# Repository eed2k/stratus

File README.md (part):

Stratus Weather Server

Version 2.2.1
Developer: Lukas Esterhuizen
Contact: esterhuizen2k@proton.me

Stratus, all software forming part of Stratus, and all associated hardware
designs are the property of METRON (PTY) LTD | Inteltronics. All rights
reserved.

A professional, multi-vendor web application for weather station management, data collection, and real-time monitoring. Stratus connects to Campbell Scientific dataloggers and a range of IoT/cloud weather platforms, then turns raw observations into rich meteorological, agricultural, aviation, fire-risk and wind-energy analytics.

---

Station & Protocol Support

This section is deliberately split into what is running against real hardware
today and what is implemented and mapped but not yet in service here, because the
difference matters when you are choosing how to connect a station.

In production use, exercised against real hardware:

- Campbell Scientific (PakBus) over TCP/IP - native PakBus implementation, including clock sync and scheduled or on-demand collection
  - Supported dataloggers: CR300, CR310, CR350, CR1000, CR1000X, CR1000Xe
- Dropbox sync - watches a folder and ingests a logger export whenever it changes. This is how the cellular sites actually deliver data: the logger writes to Dropbox and Stratus reads it. Read-only; Stratus never writes to your Dropbox
- HTTP POST ingest - the station pushes readings to a per-station endpoint
- Manual file import - TOA5 or CSV upload for bulk history
- RIKA cloud (v2 API) - session login with farm/device discovery, polled every 30 minutes to match the vendor's own update rate

On the RIKA poll specifically: the device endpoint is intermittently slow, and a
half-hourly poll means a single slow response used to cost a full half-hour of
data. Transient faults (timeouts, connection resets, transient DNS, and the busy
gateway statuses 429/502/503/504) are now retried three times with backoff inside
a budget that cannot overlap the next poll. Conditions that would fail identically
on a retry, such as bad credentials, are surfaced immediately instead. A
successful read also clears the last-error line on the settings panel, which
previously persisted through every later healthy poll because it was only ever
cleared when a station reconnected.

Vendor-mapped, implemented but not in production use here:

Each of these has its own response parser and field mapping in
`server/protocols/httpAdapter.ts`, including the unit conversions the vendor's
own units require. They are not bare REST endpoints.

- Arduino IoT Cloud - OAuth2 client-credentials against Thing properties. Properties are matched by name onto temperature, humidity, pressure, wind speed and direction, gust, rainfall, solar radiation, UV, dew point, battery, soil temperature and moisture, PM2.5, PM10 and CO2
- Stratus Logger - Metron's own datalogger board, reporting over LoRa or Sigfox. The LoRa uplink decoder and the generic MQTT/HTTP REST path exist for this board; the hardware design lives in `StratusLoggerV1[metron]/`
- WeatherLink (Davis) - authenticated with an API key and secret, sensor blocks mapped per sensor, with Fahrenheit to Celsius, inches of mercury to hPa and miles per hour to metres per second applied
- CampbellCloud - bearer token, Campbell field names (`AirTemp_C`, `RH`, `BP_mbar`, `WS_ms`, `WD`, `WS_max`, `Rain_mm`, `Solar_Wm2`, `BattV`) mapped to the canonical fields
- ThingSpeak - channel feeds, `field1` through `field8` mapped in the conventional order
- Blynk - token in the query string, virtual pins `V0` through `V5` mapped in order
- OpenWeatherMap - key sent as `appid`, `units=metric` requested when the endpoint does not already specify it, station pressure (`grnd_level`) preferred over the sea-level value, wind direction taken from `wind.deg`, precipitation from the one or three hour rain or snow total, and temperature normalized whether the endpoint returns Celsius, Fahrenheit or Kelvin

One gap, stated plainly rather than implied: bulk station **discovery**
against Campbell Cloud is not implemented. `fetchCampbellStations` raises an
explicit error telling you to use a direct PakBus connection. Collecting data
from a Campbell Cloud endpoint you configure yourself does work, per the mapping
above; it is only the "list every station on the account for me" step that is
absent.

---

Real-Time Monitoring Dashboard

- Live Dashboard - Real-time weather visualization with auto-refresh and data-freshness indicators
- Configurable Layout - Per-user dashboard configuration panel to show/hide and reorder cards
- Auto-Adjusting Sections - Cards and charts hide automatically when their data fields are unavailable
- Current Conditions - All current readings at a glance with last-update time
- Station Map - OpenStreetMap integration showing station location
- Connection Health - Connection status, data freshness, and staleness warnings
- Alarms - Configurable threshold alarms with optional email notifications
- Quick Time Ranges - 1h, 6h, 12h, 24h, 48h, and 7d views
- Interactive Charts - Temperature, humidity, pressure, solar radiation, and rainfall history

Navigation:

The sidebar is text only, with no icons, and every section is permanently
expanded: no disclosure arrows and nothing to collapse. Every destination stays
visible in the same place on every visit, so the menu can be navigated from
memory rather than by opening things to look inside. Indentation carries the
grouping.

Order runs from live monitoring, through what you produce from the data, to
configuration:

1. Active Stations (the landing page, and where every session starts)
2. AS3935 - admin panel, lightning demo, information centre
3. Forecast - overview, dashboard, accuracy
4. Data and Reports - historical export, report generation, report scheduling
5. Settings - station setup, user management, alerts, system settings
6. About Stratus

Chart styling is shared across the estate. The lightning console is Python with
no bundler, but it vendors the same chart library and mirrors the Stratus
conventions (dashed grid at low opacity, no tick marks, no axis lines, matching
stroke weights and the same palette from `shared/chartColors.ts`), so moving
between the two consoles does not feel like moving between two products.

---

Meteorological & Derived Metrics

Stratus computes a large set of derived values from raw observations:

- Dew Point - Magnus formula when not reported by the station
- Sea Level Pressure (QNH) - Hypsometric adjustment from station pressure and altitude (RIKA stations that report SLP directly are handled in reverse)
- Air Density - From temperature, pressure, and humidity
- Density Altitude - With METAR-style flight-category classification
- Reference Evapotranspiration (ETo) - FAO-56 Penman-Monteith
- Water Balance - Rainfall versus ETo
- Heat Index / Wind Chill / Feels-Like - Apparent temperature calculations
- Heat Stress (WBGT) - Wet Bulb Globe Temperature
- Atmospheric Stability - Pasquill-Gifford stability class
- Air Quality Index - AQI from PM2.5 / PM10 (e.g. RIKA particulate sensors)
- Rainfall Intensity & Yearly Totals - With per-station cumulative-counter offset correction
- Weather Trend Analysis - Current values versus historical average

Agriculture:

- Growing Degree Days (GDD) - Accumulated heat units for crop modeling
- Chill Units - Accumulated cold-hours for dormancy/fruiting models

Fire risk:

- Lowveld Fire Danger Index (LFDI) - Official SAWS/Namibia AFIS formula: (BI + WF) x RCF
- Fuel moisture estimation and component fire-danger scoring

---

Nano-Climate Forecast

A separate service at forecast.stratusweather.co.za. Pure-Python FastAPI with
server-rendered SVG, no bundler, capped at 320 MB.

The method is a station's own record CORRECTING a model background, which is why
it is called nano-climate rather than a forecast feed. A mesoscale model knows a
front arrives on Thursday; it does not know this mast sits in a hollow that pools
cold air. The station record is the part that knows.

- Model background - Vaisala Xweather, on by default for a new station with all nine engine variables. Nothing is fetched until a station has coordinates, so an unpositioned station cannot spend the access budget
- Station history - harmonic climatology, damped anomaly persistence and an analog ensemble over a rolling 35-day window. Data older than that does not enter a forecast; the window is deliberate, so a season-old regime cannot dominate the current one
- Learned site correction - `adaptive.py`. A decaying average per station, variable, provider, lead bucket and time-of-day bucket, updated from the station's own verified forecasts
- Verification - MAE, bias, CRPS, rank histograms and reliability diagrams, scored against the station's own observations, with a method-version hash so a change of method is visible rather than averaged into the history

On the learned correction, measured rather than claimed. Across eight months of
Quaggasklip's record, over identical base hours with and without it, at lead
1-24h: solar radiation error fell 17 percent, humidity 2 percent, pressure and
temperature 1 percent each, wind direction unchanged, and wind speed and gust
each rose about 2 percent. It only acts where an offset is a meaningful share of
the error, which is why it declines to touch a variable whose error is mostly
scatter. Rainfall is excluded outright: its error is intermittency, not offset,
and shifting every hour by a learned millimetre invents drizzle on dry days.

Backfilling is how a new station gets a skill history without waiting: forecasts
are re-issued from past base hours using only the data that existed before each
one, so they can be scored immediately. Issued oldest first, which makes a
backfill with the correction enabled a walk-forward test rather than a claim.

---

Wind Analysis & Wind Energy

- Wind Rose Charts - Direction-frequency distribution over 60 min, 24h, 48h periods
- Wind Speed vs Gust (24h) - Fixed 24-hour comparison chart
- Wind Speed Scatter - Polar plot with color-coded speed classes
- Wind Compass - Real-time direction and speed with cardinal labels
- Beaufort Scale - WMO Beaufort classification of current wind
- Crosswind / Headwind - Runway-relative components for aviation
- Turbulence Intensity - From wind-speed standard deviation
- Wind Power Density - Available wind energy (W/m²) using station-specific air density
- Cumulative Wind Energy Potential - Daily kWh/m² with time-interval integration
- Weibull Distribution - Fitted wind-speed distribution
- Annual Energy Production (AEP) - Estimated turbine yield from the Weibull fit

---

Solar & Power Monitoring

- Solar Position Tracking - Sun elevation, azimuth, nautical dawn/dusk
- Solar Radiation - Incoming shortwave with history
- Solar Power Harvest - Estimated harvestable solar energy
- MPPT Charger Monitoring - Solar charge-controller telemetry
- Battery Monitoring - Logger battery voltage with LiFePO4 status and charging detection

---

Lightning Detection System (LDS)

A separate but linked subsystem: an AS3935 lightning sensor on a Raspberry Pi
Zero W reporting into a multi-tenant FastAPI console (Lightning Alert Console
v1.0), deployed alongside Stratus behind the same Traefik proxy.

Detector (Raspberry Pi Zero W + AS3935):

- SPI-attached AS3935 franklin lightning sensor with startup calibration self-check
- Hourly heartbeat plus an immediate ping on every in-range strike, reporting CPU temperature and load
- Low-power configuration: HDMI, Bluetooth and onboard LEDs disabled, CPU governor tuned
- USB gadget ethernet on a fixed address, so a card with no working wifi is still recoverable over the single USB cable
- Provisioned by cloud-init from the SD card boot partition (see `RPiZero SD Card/`)

Admin console:

- Multi-tenant: each client gets its own panel at `/<slug>/`, with a platform-level management console at the root for creating clients and assigning newly-reporting detectors
- Recipients, groups and per-tenant alert configuration with an alert cooldown
- SMS alerts via Clickatell, with a master on/off switch. The gateway is platform infrastructure and is not exposed in client panels
- Monthly PDF reports (WeasyPrint) with vector charts: CPU trend, distance histogram, energy bands, uptime gauge and storm activity
- Event history with per-event delivery detail

Detector provisioning:

A detector files itself under the platform tenant on its first heartbeat and is
invisible to every client panel until an admin assigns it on the platform
console's Detectors page. That is deliberate rather than incidental: an unclaimed
unit has no owning client, so there is no recipient list to consult and no alert
is sent for it. Assigning a unit also re-files its strike history, heartbeat
samples and calibration records, so a client is not handed a live detector whose
past begins on the day of the handover.

Who can see what:

- Stratus Admin may enter any panel. The session is not pinned for them, so their effective tenant follows the URL
- A client login is pinned to its own tenant. A mismatch between the cookie, the user record and the URL is treated as not-signed-in for that panel rather than an error that would confirm the panel exists
- A client admin sees every login in their own panel and may add and remove them
- An operator sees operator and viewer logins only, never administrators, and has no add or remove controls. Knowing which accounts hold admin rights is the useful half of an attack on them
- A viewer sees no login list, matching how the panel already treats a read-only account elsewhere

Creating a login sends nothing. There is no outbound mail path in this console at
all, which a test enforces by asserting no mail library is importable anywhere in
the package: an operator is created with a password the admin chooses and is told
by whatever means the client prefers. Adding an SMS recipient likewise sends no
confirmation message to that number.

POPIA: a recipient's number is masked to its country prefix and last two digits
before it reaches a log, because container logs are rotated to disk, swept into
backups and read by platform staff who have no relationship with the client's
staff. The full number stays in the message log the client is entitled to see on
their own event page, scoped to their tenant.

Storm activity display:

Recorded strikes are grouped into five proximity bands, nearest first, each drawn
as a small cumulonimbus that flashes more often the busier the band. The block
under each cloud gives the strike count with the peak, mean and lowest intensity
recorded in that band.

- Distance bands: `<= 1 km` (overhead), `< 10 km`, `< 20 km`, `< 30 km`, `30-40 km`
- Selectable window from 1 h to 24 h
- Energy bands (Low / Moderate / High / Extreme) are quarters of the sensor's 21-bit full scale

Two measurement caveats are stated on the display itself rather than left to the
reader to discover:

- The AS3935 measures distance but **not bearing**. Nothing in the display is placed in a compass direction, because any angle would be invented. This is why the view is a proximity ordering and not a map.
- Reported "energy" is a relative sensor value for comparing strikes with each other. It is not joules, and it is not calibrated to any physical unit.

Distance is reported in 15 discrete steps at a manufacturer-rated accuracy of
+/- 4 km, so a strike can legitimately land in an adjacent band.

The band aggregation lives in one place, `LDS ADMIN/app/metrics.py::distance_band_summary`.
Both the live dashboard (`/data/strikes`) and the PDF renderer
(`charts.py::storm_bands_svg`) consume it, so the panel and the report cannot
disagree about how many strikes fell in each band.

---

Reports & Data Export

- History & Analysis - View and analyze data across configurable time ranges
- Report Generation - Export to CSV and PDF (server-side PDF with charts, wind roses, summary tables)
- Scheduled Reports - Password-protected /reports portal; daily/weekly/monthly schedules run via node-cron and email PDF reports
- Stratus Digest - Optional scheduled plain-text/HTML digest email (station status, alarms, temperature, rainfall, wind)
- Data Completeness - Coverage metrics highlighting gaps in the record

How a PDF report is laid out:

Page one is ordered so the document identifies itself before it presents any
figures, and so a reader who only wants the numbers never has to page past the
artwork to reach them.

1. Title: `<Station> Weather Data Report | <period>`
2. Site details, one fact per line and no bullets: location, coordinates, elevation in metres AMSL, and the reporting period as absolute dates
3. Two views of the site side by side, each half the text width, both pinned at the station: a close satellite frame for mast surroundings and exposure, and a wider street map for roads and nearby settlements
4. The min / average / maximum / total statistics table

The period appears twice on purpose. The title carries the relative wording
("Last 30 days"), which is what an operator asks for but which stops being true
once the PDF is filed; the details block carries the absolute dates that keep an
archived report self-describing.

The map pin is placed from fractional Web Mercator tile coordinates, so it lands
on the mast rather than at the centre of the fetched tile block. Both frames come
from the same Esri host, which means one egress rule and one tile scheme. Imagery
is never load-bearing: if the tiles cannot be fetched the table simply moves up
the page, because a report missing its site photograph is still a usable report.

There is no heading above the statistics table. It used to repeat the station name
and period already given in the title, and the table's own column headers say what
the columns are. A table continuing onto another page is still marked, so a reader
landing mid-table knows what they are looking at.

Report text is plain regular Arial throughout, in black. No grey, no bold, and no
em or en dashes anywhere in the output.

---

Calibration & Compliance

- Calibration Management - Track calibration records, due dates, and resolution presets (e.g. rainfall tipping-bucket resolution)
- Per-Station Rainfall Offsets - Suppress phantom rain from cumulative counters that pre-date integration
- Compliance Tracking - Data quality flags and certifications
- Audit Logging - Comprehensive logging of security-relevant events

Rainfall interpretation, and why it is configured rather than guessed:

CRBasic programs and cloud vendors record rain in incompatible ways, and the same
number means different things depending on which. A per-interval field holds the
rain for that scan and must be summed. A cumulative counter holds a running depth
and must be differenced. Reading one as the other does not fail loudly; it
silently returns a plausible but wrong total.

So each station carries an explicit `rainfall_type` in `station_calibration`,
maintained from the admin calibration page, and every totalling path reads it:

- `incremental` - sum the values
- `cumulative_yearly` / `cumulative_lifetime` - sum the positive steps, rejecting counter resets and single-sample glitches larger than any real interval of rain
- `tip_count` - multiply raw tips by the station's `tipFactor`

`auto` remains only as a fallback heuristic for a station nobody has configured,
and it is genuinely unreliable on a fast logger: a one-minute per-interval field
that returns to zero between showers looks enough like a counter to be misread.
Measured on Quaggasklip over 30 days, the heuristic reported 14.5 mm where the
configured incremental reading gives 26.3 mm, which is what a direct SQL sum of
the field confirms. Configure the station.

Because that lookup is synchronous against an in-memory snapshot, an empty
snapshot is indistinguishable from "no calibration" at the call site. Report
rendering therefore awaits the snapshot load before totalling anything, so a
report generated moments after a restart cannot quietly take the fallback path.

Field totals are computed server-side with SQL over the full range, never from the
decimated series a chart is drawn from. Decimation drops records, and for an
accumulating quantity a dropped record is dropped rain.

---

Monitoring & Notifications

Email delivery is handled via MailerSend:

- User Invitations - Email invites with secure setup links
- Password Reset - Self-service reset emails (rate limited)
- Alert Notifications - Email alerts when alert thresholds trigger
- Staleness / Downtime Monitor - Optional admin alerts when a station stops sending data
  - Disabled by default (STALENESS_ALERTS_ENABLED=false); enable explicitly per deployment
- Scheduled Reports & Digest - Automated PDF/text emails on a cron schedule
- Professional HTML Templates - Branded, clearly worded messages

---

Shared Dashboards

- Public Sharing - Generate shareable links for stations
- Compact Dashboards - Optional single-screen share links (no scrolling) with primary metric tiles, 1h and 24h wind roses, and live temperature/humidity and battery/solar charts. Ideal for TVs, monitors and laptops
- Password Protection - Optional password for shared dashboards
- Expiration Control - Set expiry dates for shared links
- View-Only Access - Shared viewers cannot edit

---

Security Features

- Rate Limiting - Protection against brute-force login and password-reset attempts
- Secure JWT Tokens - Cryptographically signed tokens with environment-configurable secrets
- Password Hashing - bcrypt with configurable salt rounds
- Input Validation - Zod schema validation on API endpoints
- HTTPS Enforcement - TLS for all traffic
- Session Management - Secure sessions with automatic recovery
- Audit Logging - Security-event logging
- Content Security Policy - The LDS console runs under `script-src 'self'` with no exceptions: chart bundles are vendored rather than pulled from a CDN, and there are no inline scripts
- Secret Scanning - `python deploy/scan_secrets.py` checks every file git could commit (tracked plus non-ignored untracked) for credentials, and exits non-zero on a finding. Run it before pushing
- Not Indexed, Anywhere - every surface refuses search engines on every response type, not only on its HTML. A meta tag reaches a crawler that parses markup; it does nothing for a JSON endpoint, a generated PDF, a chart image or a redirect. So `X-Robots-Tag: noindex, nofollow, noarchive, nosnippet, noimageindex, notranslate` is set by the server on all five surfaces, backed by a meta tag on the pages and a `robots.txt` on every host. Shared dashboard links are covered by the same header

TLS is issued and renewed by Traefik alone, from its own ACME store. Nothing else
on the host may hold a certificate for these names: a second ACME client cannot
succeed, because Traefik owns ports 80 and 443, and every failed validation it
makes counts against Let's Encrypt's per-hostname failure limit for the same
names Traefik has to renew. A leftover certbot installation was doing exactly
that and is now disabled and masked.

Credentials are kept out of the repository by design. Anything holding a real
secret is gitignored and shipped as a `.example` template instead: the detector's
cloud-init files (wifi PSK, user password hash) and every `.env` variant. A
credential committed once stays recoverable from git history even after the file
is deleted, so the safer default is never to commit it.

---

User Management

- Admin and User Roles - Admins have full access; users see only assigned stations
- Station Assignment - Assign specific stations to individual users
- User Invitation System - Invite via email with secure setup links
- Password Reset - Self-service reset via email (rate limited)
- Account Settings - Self-service profile and password management

---

Hosting

Stratus is designed for cloud VPS deployment for 24/7 availability.

- Recommended: Vultr, Hetzner, Linode, DigitalOcean
- 1-2 vCPU, 2-4 GB RAM sufficient
- Docker containerized deployment (Traefik reverse proxy)
- PostgreSQL database (Neon serverless supported; SQLite supported for local development)
- Automatic restart on failure

---

Environment Variables

Key environment variables (see .env.example for the full annotated list):

```
# Database (Required)
DATABASE_URL=postgresql://user:password@host:port/database

# Server
PORT=5000
NODE_ENV=production

# Security (Required in production)
CLIENT_JWT_SECRET=<generate with: openssl rand -hex 32>
APP_BASE_URL=https://yourdomain.com

# Admin Account (Required in production)
STRATUS_ADMIN_EMAIL=admin@example.com
STRATUS_ADMIN_PASSWORD=<strong-password>
STRATUS_ADMIN_NAME=Admin User

# Email (MailerSend - optional)
MAILERSEND_API_KEY=your_api_token
MAILERSEND_FROM_EMAIL=noreply@yourdomain.com
MAILERSEND_FROM_NAME=Stratus Weather
MAILERSEND_ALERTS_EMAIL=alerts@yourdomain.com

# Scheduled Digest (optional, requires MailerSend)
DIGEST_ENABLED=true
DIGEST_RECIPIENT=recipient@yourdomain.com
DIGEST_CRON=0 8 * * 1,5   # Mon/Fri 08:00 (Africa/Johannesburg)

# Staleness / Downtime Monitor (optional, disabled by default)
STALENESS_ALERTS_ENABLED=false
STALENESS_CHECK_INTERVAL=900000   # 15 min
STALENESS_THRESHOLD=7200000       # 2 h
STALENESS_COOLDOWN=21600000       # 6 h

# Dropbox Integration (optional)
DROPBOX_APP_KEY=your_app_key
DROPBOX_APP_SECRET=your_app_secret
DROPBOX_REFRESH_TOKEN=your_refresh_token
DROPBOX_FOLDER_PATH=/CR300/Data
```

---

Project Structure

```
client/             React frontend (Vite + TypeScript + Tailwind)
  src/
    components/     UI components (dashboard cards, charts, station setup, sidebar)
    pages/          Route pages (Dashboard, History, Reports, Alarms, Calibration, Settings, ...)
    hooks/          Custom React hooks (useAuth, useMobile)
    lib/            Utility functions and constants
server/             Express backend (TypeScript)
  campbell/         PakBus protocol and datalogger management
  compliance/       Audit and compliance routes
  parsers/          TOA5/Campbell data parsers
  protocols/        Protocol manager + HTTP/LoRa adapters (Rika, Arduino, Campbell, WeatherLink, ...)
  services/         Dropbox sync, email, staleness monitor, report scheduler, digest, PDF, calibration
  shares/           Shared dashboard routes
  station-setup/    Connection validation, service detection, integration service
shared/             Shared types and utilities
  utils/            Calculation functions (LFDI, solar, ETo, air density, AQI, WBGT, Weibull, AEP, ...)
assets/             Application icons
deploy/             Deployment scripts, Docker config, backups, secret scanner
scripts/            Dropbox auth and documentation generation

forecast/           Nano-climate forecast service (separate deployment)
  app/              FastAPI + Jinja2, server-rendered SVG charts, no bundler
    engine.py       Blending, harmonics and the analog ensemble
    adaptive.py     Learned per-site bias correction (see below)
    plain.py        Plain-language outlook (day cards and sentences)
    providers/      NWP adapters (Xweather only) and the per-variable opt-in
  tests/            pytest suite
  README.md         What it is, which models it uses, how to read it

info-centre/        Static documentation site (nginx)
lightning-demo/     Static lightning demo site (nginx)
Beacon/             Pilot-light/beacon controller for the lightning system
Emulator/           Bench emulator for the AS3935 detector (Arduino + Pi)
BeagleBone/         Kiosk that boots a BBB into a wall dashboard over HDMI

StratusLoggerV1[metron]/  Stratus Logger hardware design (KiCad): the in-house
                          datalogger board, LoRa/Sigfox uplink
AS3935/             Lightning detector (Pi Zero W + AS3935) firmware
AS3935handheld/     Handheld lightning detector hardware design (KiCad)
RPiZero SD Card/    Detector boot partition: service, installer, config.txt with
                    SPI enabled and the low-power options, cloud-init templates
                    as *.example (the real files hold credentials and are
                    gitignored), and FLASH_FROM_SCRATCH.md

LDS ADMIN/          Lightning Alert Console (FastAPI, separate deployment)
  app/
    routes/         Web pages, JSON data endpoints, detector ingest API
    templates/      Jinja2 templates (server-rendered, no SPA)
    static/         style.css, app.js, js/cpu-chart.js, js/storm-view.js
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
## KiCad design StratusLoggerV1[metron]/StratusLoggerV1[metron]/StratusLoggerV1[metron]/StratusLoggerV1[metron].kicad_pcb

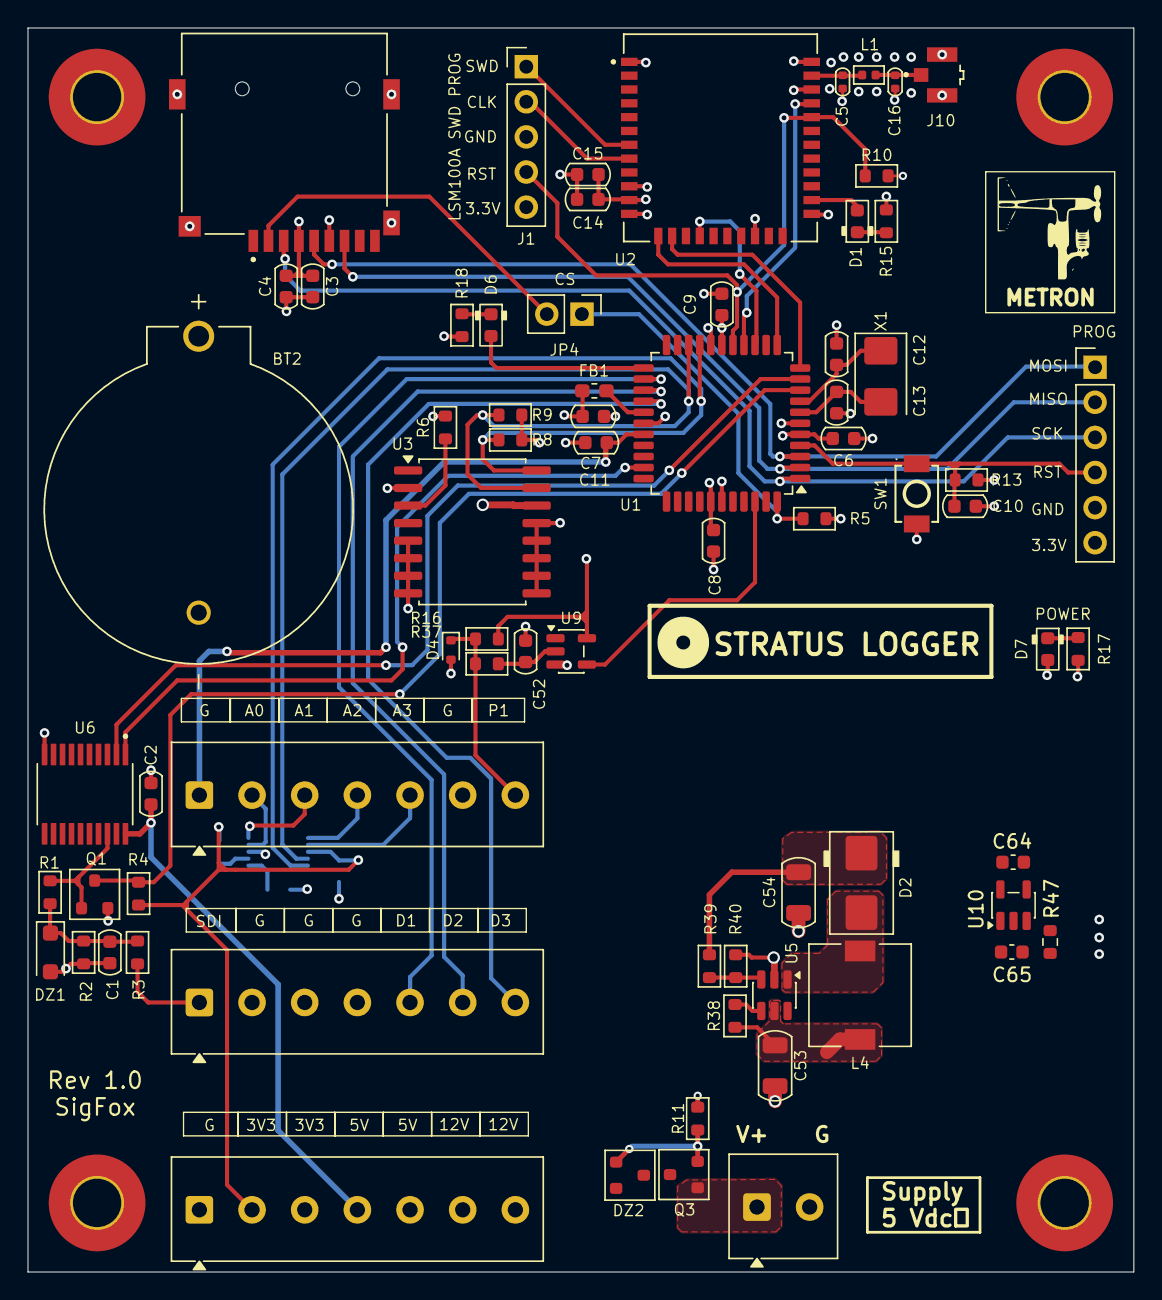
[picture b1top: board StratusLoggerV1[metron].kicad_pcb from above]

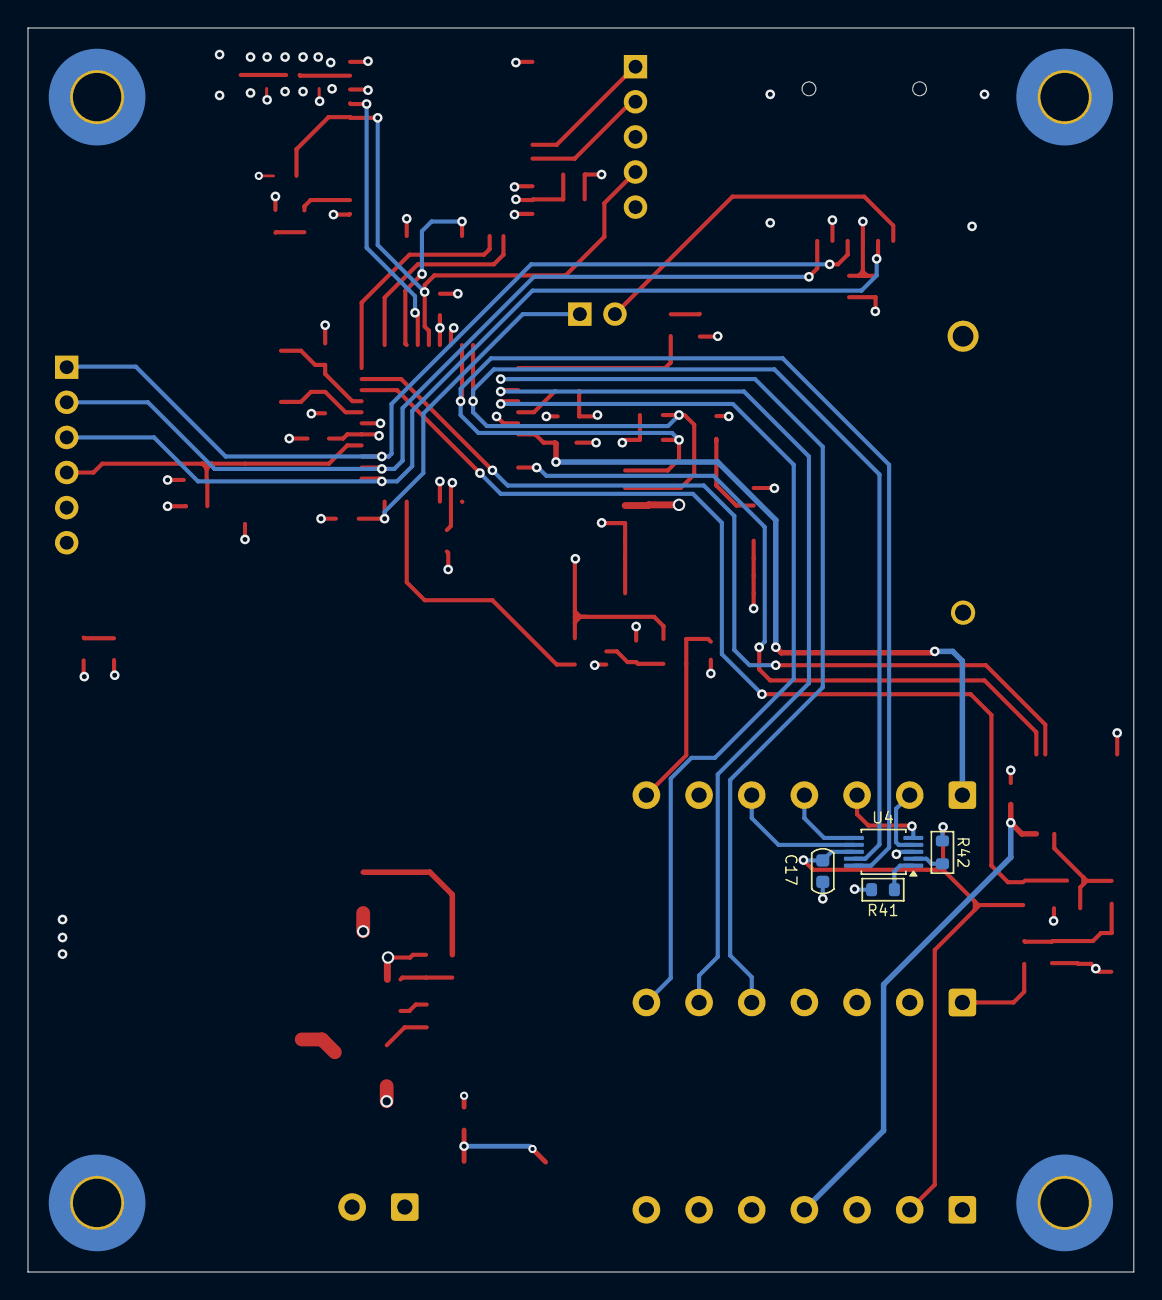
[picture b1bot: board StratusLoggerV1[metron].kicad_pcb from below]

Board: 4 copper layers, 80.0 x 90.0 mm, 80 parts (4 on the bottom side), 56 nets.

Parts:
BT2: BS-7; BAT_BS-7
C1: 3.3nF; C_0603_1608Metric
C2, C3, C7, C8, C9, C10, C11, C15, C17: 100nF; C_0603_1608Metric
C4, C6, C14: 10uF; C_0603_1608Metric
C5, C16: NC; C_0402_1005Metric
C12, C13: 18pF; C_0603_1608Metric
C52: 1u; C_0603_1608Metric
C53, C54: 22uF; C_1206_3216Metric
C64: 4.7u; C_0603_1608Metric
C65: 10u; C_0603_1608Metric
D1, D6, D7: LED; LED_0603_1608Metric
D2: SS24; D_SMB
D4: VESD05A1-02V-G3-08; D_SOD-523
DZ1: 1N4737; D_SOD-123F
DZ2: BZX84-C15; SOT-23
FB1: FerriteBead; L_0603_1608Metric_Pad1.05x0.95mm_HandSolder
H1, H2, H3, H4: MountingHole; MountingHole_3.5mm_Pad_TopBottom
J1: Conn_01x05_Pin; PinHeader_1x05_P2.54mm_Vertical
J2: MSD-1-A; CUI_MSD-1-A
J4: Conn_01x06_Pin; PinHeader_1x06_P2.54mm_Vertical
J6: Screw_Terminal_01x02; TerminalBlock_Phoenix_MKDS-1-2-3.81_1x02_P3.81mm_Horizontal
J8, J9, J14: Screw_Terminal_01x07; TerminalBlock_Phoenix_MKDS-1-7-3.81_1x07_P3.81mm_Horizontal
J10: 20279-001E-03; IPEX_20279-001E-03
JP4: Jumper_2_Open; PinHeader_1x02_P2.54mm_Vertical
L1: OR; L_0402_1005Metric
L4: 22uH; L_7.3x7.3_H3.5
Q1: BSS123L; SOT-23
Q3: DMP3098L; SOT-23
R1, R3: 510R; R_0603_1608Metric
R2: 200K; R_0603_1608Metric
R4, R8, R9: 4.7K; R_0603_1608Metric
R5, R6, R10, R11, R13, R16, R37, R42: 10K; R_0603_1608Metric
R15: 560R; R_0603_1608Metric
R17, R18: 1K; R_0603_1608Metric
R38: 8.45K; R_0603_1608Metric
R39: 43K; R_0603_1608Metric
R40: 2.2K; R_0603_1608Metric
R41: 0R; R_0603_1608Metric
R47: 100k; R_0603_1608Metric
SW1: TS-1088-AR02016; SW-SMD_L3.9-W3.0-P4.45
U1: ATmega1284P-A; TQFP-44_10x10mm_P0.8mm
U2: LSM100A; XCVR_LSM100A
U3: DS3231M; SOIC-16W_7.5x10.3mm_P1.27mm
U4: ADS1115IDGS; TSSOP-10_3x3mm_P0.5mm
U5: MT3608; SOT-23-6
U6: SN74HCT240PWR; SOP65P640X120-20N
U9: SN74LVC1G17; SOT-23-5
U10: XC6220B331MR; SOT-23-5
X1: 11.0592 MHz; Crystal_SMD_5032-2Pin_5.0x3.2mm

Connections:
3V3DC: C3.1, C4.1, C6.1, C7.1, C8.1, C9.1, C14.1, C15.1, C17.1, C64.1, D7.2 (A), FB1.2, J1.5, J2.4 (VDD), J4.6, J14.2, J14.3, R4.2, R5.2, R6.2, R8.2, R9.2, R10.2, R13.2, R16.1, R42.1, U1.5 (VCC), U1.17 (VCC), U1.38 (VCC), U2.11 (VDD), U3.2 (VCC), U4.8 (VDD), U9.5 (VCC), U10.5 (VOUT)
5VDC: C2.1, C53.1, C65.1, DZ2.3 (K), J14.4, J14.5, L4.1, Q3.3 (S), R38.1, U5.5 (IN), U6.20 (VCC), U10.1 (VIN)
12VDC: C54.1, D2.1 (K), J14.6, J14.7, R39.1
/12V_SW: D2.2 (A), L4.2, U5.1 (SW)
/VIN: J6.1, Q3.1 (D)
A0: J9.2, U4.4 (AIN0)
A1: J9.3, U4.5 (AIN1)
A2: J9.4, U4.6 (AIN2)
A3: J9.5, U4.7 (AIN3)
AREF: C11.1, J9.1, U1.29 (AREF)
CS: J2.2 (CD/DAT3), JP4.2 (B)
GND: BT2.-, C1.2, C2.2, C3.2, C4.2, C5.2, C6.2, C7.2, C8.2, C9.2, C10.2, C11.2, C12.2, C13.2, C14.2, C15.2, C16.2, C17.2, C52.2, C53.2, C54.2, C64.2, C65.2, D4.2 (A2), DZ1.2 (A), J1.3, J2.6 (VSS), J2.G1 (COVER_GND), J2.G2 (COVER_GND__1), J2.G3 (COVER_GND__2), J2.G4 (COVER_GND__3), J4.5, J6.2, J8.2, J8.3, J8.4, J9.6, J10.2, J10.3, J14.1, Q1.2 (S), R2.1, R11.1, R15.1, R17.1, R18.1, R40.2, R41.2, R47.2, SW1.1, U1.6 (GND), U1.18 (GND), U1.28 (GND), U1.39 (GND), U2.1 (GND), U2.10 (GND), U2.12 (GND), U2.20 (GND), U2.23 (GND), U2.32 (GND), U2.34 (GND), U3.5 (GND), U3.6 (GND), U3.7 (GND), U3.8 (GND), U3.9 (GND), U3.10 (GND), U3.11 (GND), U3.12 (GND), U3.13 (GND), U4.3 (GND), U5.2 (GND), U6.10 (GND), U9.3 (GND), U10.2 (GND)
LED: D6.2 (A), U1.23 (PC4)
LSM_BOOT: U1.15 (PD6), U2.31 (BOOT)
LSM_RESET: J1.4, R10.1, U1.16 (PD7), U2.30 (~RST)
LSM_UART_RX: U1.12 (PD3), U2.13 (PA3/UART2_RX)
LSM_UART_TX: U1.11 (PD2), U2.14 (PA2/UART2_TX)
LSM_WAKE: U1.14 (PD5), U2.16 (PA0/BUT1)
MCU_RESET: C10.1, J4.4, R13.1, SW1.2, U1.4 (~RESET)
MISO: J2.7 (DAT0), J4.2, U1.2 (PB6)
MOSI: J2.3 (CMD), J4.3, U1.1 (PB5)
unnamed: C16.1, J10.1, L1.2
unnamed: C52.1, R37.2, U9.2
unnamed: D1.2 (A), U2.24 (PA8/LED1)
unnamed: D1.1 (K), R15.2
unnamed: D6.1 (K), R18.2
unnamed: D7.1 (K), R17.2
unnamed: C1.1, DZ1.1 (K), R1.2, R2.2, R3.1
unnamed: DZ2.1 (A), Q3.2 (G), R11.2
unnamed: JP4.1 (A), R5.1, U1.44 (PB4)
unnamed: Q1.1 (G), R1.1, U6.18 (1Y1)
unnamed: FB1.1, U1.27 (AVCC)
unnamed: C12.1, U1.8 (XTAL1), X1.1
unnamed: C13.1, U1.7 (XTAL2), X1.2
unnamed: C5.1, L1.1, U2.33 (RFOUT)
unnamed: BT2.+, U3.14 (VBAT)
unnamed: R6.1, U3.3 (~INT/SQW)
unnamed: R41.1, U4.1 (ADDR)
unnamed: R42.2, U4.2 (ALERT/RDY)
unnamed: R38.2, U5.4 (EN)
unnamed: R39.2, R40.1, U5.3 (FB)
unnamed: R47.1, U10.3 (CE)
OE: U1.32 (PA5), U6.1 (1~OE)
PC5: J8.5, U1.24 (PC5)
PC6: J8.6, U1.25 (PC6)
PC7: J8.7, U1.26 (PC7)
PULSE_IN: D4.1 (A1), J9.7, R16.2, R37.1
PULSE_MCU: U1.42 (PB2), U9.4
RXD: Q1.3 (D), R4.1, U1.9 (PD0)
SCK: J2.5 (CLK), J4.1, U1.3 (PB7)
SCL: R8.1, U1.19 (PC0), U3.16 (SCL), U4.10 (SCL)
SDA: R9.1, U1.20 (PC1), U3.15 (SDA), U4.9 (SDA)
SDI12_DATA: J8.1, R3.2
SWCLK: J1.2, U2.8 (PA14/SWCLK)
SWDIO: J1.1, U2.7 (PA13/SWDIO)
TXD: U1.10 (PD1), U6.2 (1A1)

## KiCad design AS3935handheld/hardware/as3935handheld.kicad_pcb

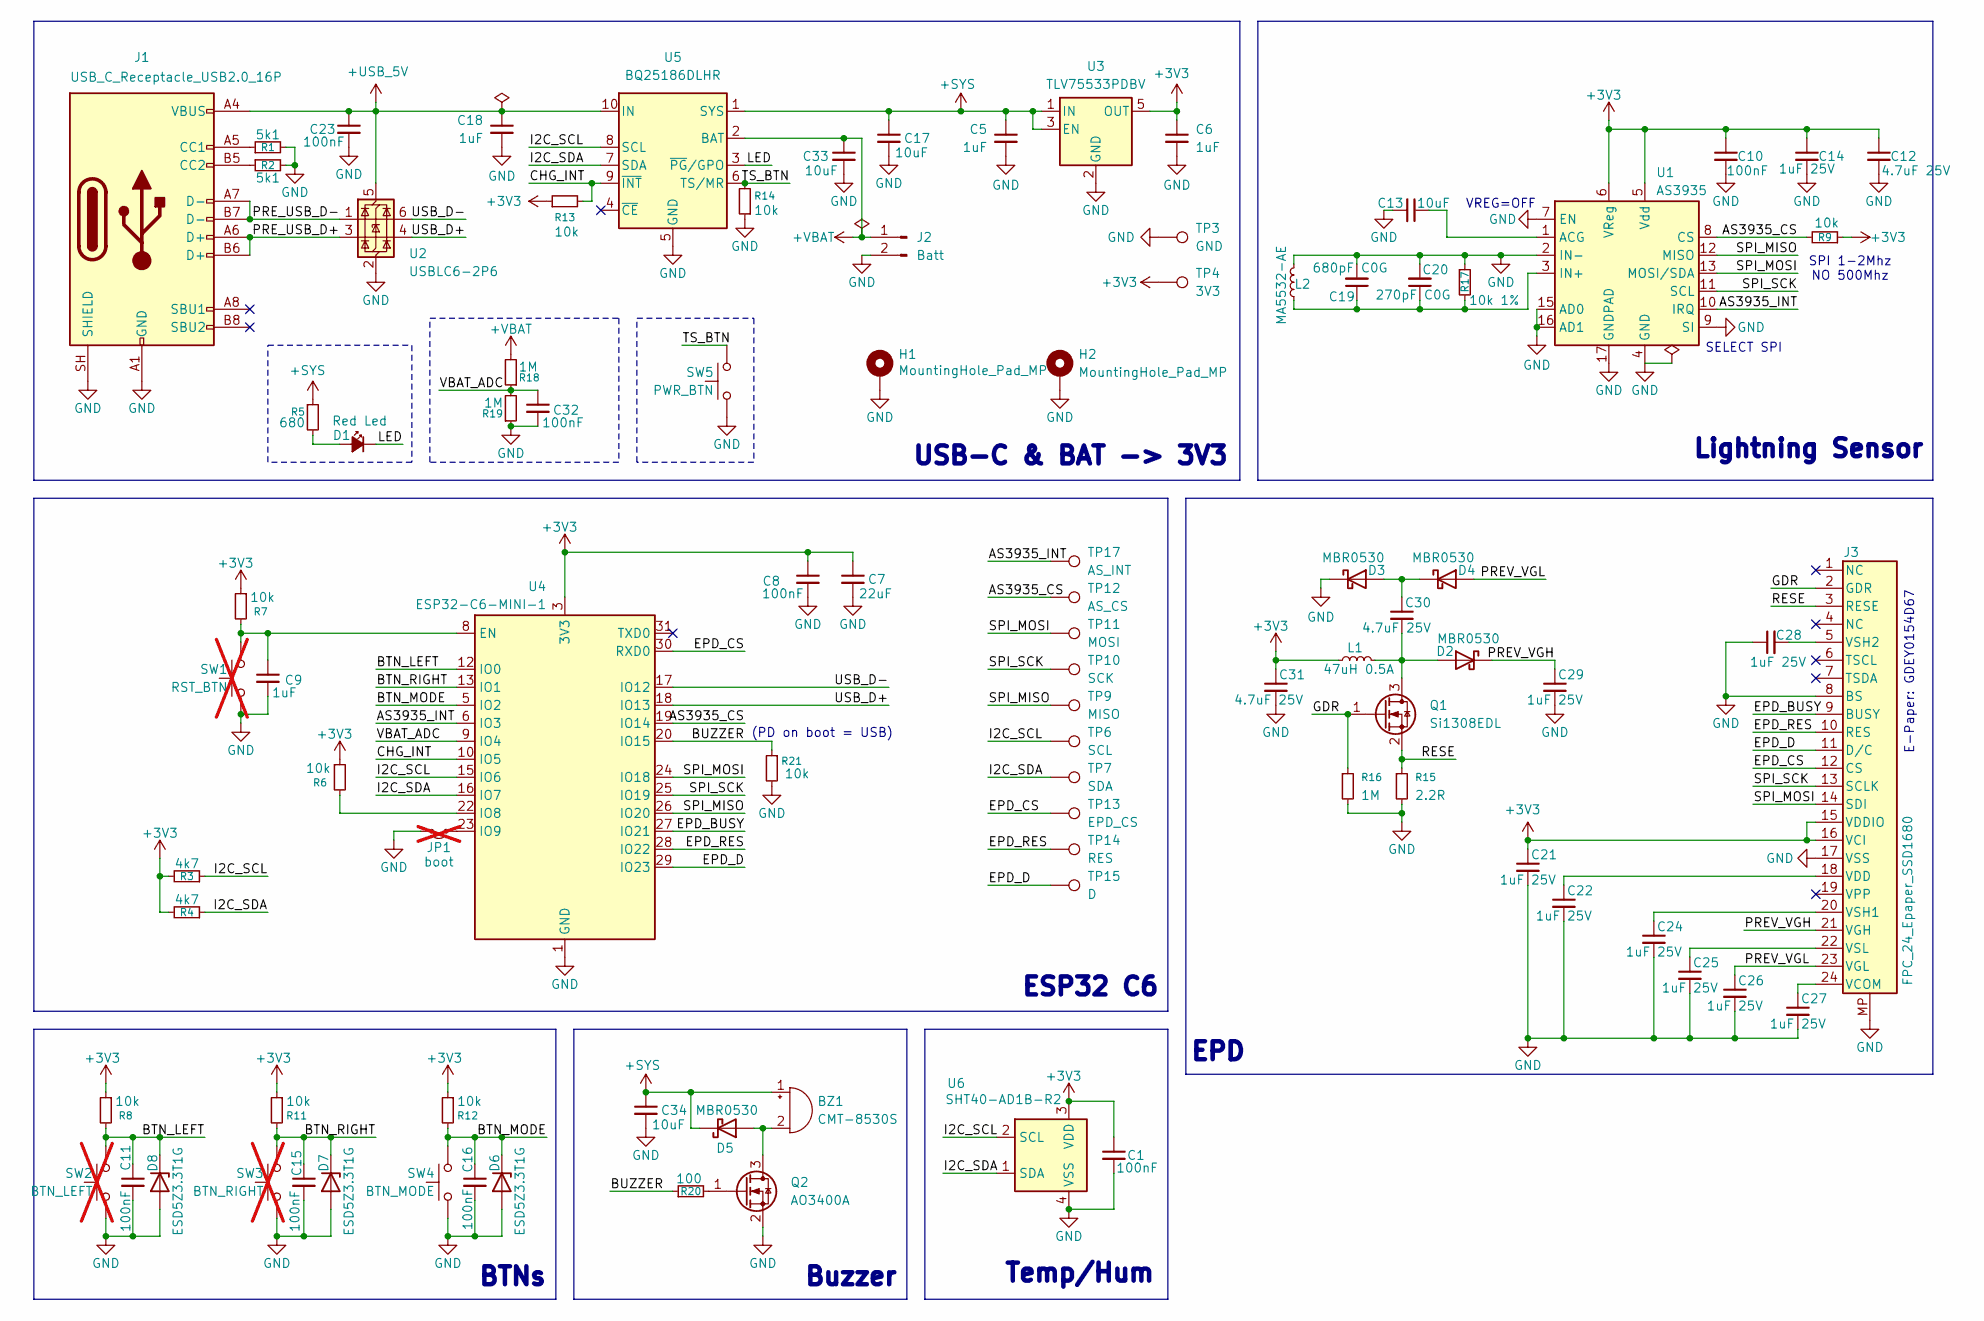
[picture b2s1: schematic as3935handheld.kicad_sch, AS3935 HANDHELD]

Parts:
BZ1: CMT-8530S; CUI_CMT-8530S-SMT; MPN CMT-8530S-SMT-TR
C1, C8, C10, C11, C15, C16, C23, C32: 100nF; C_0402_1005Metric; MPN CL05B104KO5NNNC
C5, C6, C9, C18: 1uF; C_0402_1005Metric; MPN GRM155R61E105KA12D
C7: 22uF; C_0603_1608Metric; MPN CL10A226MO7JZNC
C12, C30, C31: 4.7uF 25V; C_0603_1608Metric; MPN C1608X5R1E475K080AC
C13: 10uF; C_0402_1005Metric; MPN GRM155R61A106ME11D
C14, C21, C22, C24, C25, C26, C27, C28, C29: 1uF 25V; C_0603_1608Metric; MPN CGA3E1X7R1E105K080AC
C17, C33, C34: 10uF; C_0603_1608Metric; MPN GRM188R61E106KA73D
C19: 680pF C0G; C_0402_1005Metric; MPN GCM1555C1H681FA16D
C20: 270pF C0G; C_0402_1005Metric; MPN GRT1555C1H271FA02D
D1: Red Led; LED_0402_1005Metric; MPN QBLP595-R-2897
D2, D3, D4, D5: MBR0530; D_SOD-123; MPN MBR0530; LCSC Part C82046
D6, D7, D8: ESD5Z3.3T1G; D_SOD-523; MPN ESD5Z3.3T1G
H1, H2: MountingHole_Pad_MP; MountingHole_2.5mm_Pad
J1: USB_C_Receptacle_USB2.0_16P; USB_C_Receptacle_GCT_USB4105-xx-A_16P_TopMnt_Horizontal; MPN USB4105-GF-A
J2: Batt; JST_PH_S2B-PH-SM4-TB_1x02-1MP_P2.00mm_Horizontal; MPN S2B-PH-SM4-TB
J3: FPC_24_Epaper_SSD1680; Amphenol_F32Q-1A7x1-11024_1x24-1MP_P0.5mm_Horizontal_RevPin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; MPN F32Q-1A7H1-11024
JP1: boot; R_0402_1005Metric; MPN DNP; not fitted
L1: 47uH 0.5A; L_APV_ANR4030; MPN NR4018T470M; LCSC Part C223059
L2: MA5532-AE; Coilcraft_MA5532-AE_RFID; MPN MA5532-AED
Q1: Si1308EDL; SOT-323_SC-70; MPN SI1308EDL-T1-BE3
Q2: AO3400A; SOT-23; MPN AO3400A
R1, R2: 5k1; R_0402_1005Metric; MPN RC0402FR-075K1L
R3, R4: 4k7; R_0402_1005Metric; MPN RC0402FR-074K7L
R5: 680; R_0402_1005Metric; MPN RC0402FR-07680RL
R6, R7, R8, R9, R11, R12, R13, R14, R21: 10k; R_0402_1005Metric; MPN RC0402FR-0710KL
R15: 2.2R; R_0402_1005Metric; MPN RC0402FR-072R2L
R16, R18, R19: 1M; R_0402_1005Metric; MPN RC0402FR-071ML
R17: 10k 1%; R_0402_1005Metric; MPN RC0402FR-0710KL
R20: 100; R_0402_1005Metric; MPN RC0402FR-07100RL
SW1: RST_BTN; SW_SPST_EVQP7A; MPN EVQ-P7A01P; not fitted
SW2: BTN_LEFT; SW_SPST_SKQG_WithStem; MPN SKQGABE010; not fitted
SW3: BTN_RIGHT; SW_SPST_SKQG_WithStem; MPN SKQGABE010; not fitted
SW4: BTN_MODE; SW_SPST_SKQG_WithStem; MPN SKQGABE010
SW5: PWR_BTN; Panasonic_EVQPUM_EVQPUD; MPN EVQPUD02K; LCSC Part C388885
TP3: GND; TestPoint_Pad_D1.0mm
TP4: 3V3; TestPoint_Pad_D1.0mm
TP6: SCL; TestPoint_Pad_D1.0mm
TP7: SDA; TestPoint_Pad_D1.0mm
TP9: MISO; TestPoint_Pad_D1.0mm
TP10: SCK; TestPoint_Pad_D1.0mm
TP11: MOSI; TestPoint_Pad_D1.0mm
TP12: AS_CS; TestPoint_Pad_D1.0mm
TP13: EPD_CS; TestPoint_Pad_D1.0mm
TP14: RES; TestPoint_Pad_D1.0mm
TP15: D; TestPoint_Pad_D1.0mm
TP17: AS_INT; TestPoint_Pad_D1.0mm
U1: AS3935; MLPQ-16-1EP_4x4mm_P0.65mm_EP2.8x2.8mm; MPN AS3935-BQFT
U2: USBLC6-2P6; SOT-666; MPN USBLC6-2P6; LCSC Part C15999
U3: TLV75533PDBV; SOT-23-5; MPN TLV75533PDBVR; LCSC Part C404027
U4: ESP32-C6-MINI-1; ESP32-C6-MINI-1U; MPN ESP32-C6-MINI-1U-H4
U5: BQ25186DLHR; Texas_DLH0010A_WSON-10-1EP_2.2x2mm_P0.4mm_EP0.9x1.5mm_Therm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; MPN BQ25186DLHR
U6: SHT40-AD1B-R2; Sensirion_DFN-4_1.5x1.5mm_P0.8mm_SHT4x_NoCentralPad; MPN SHT40-AD1B-R2; LCSC Part C2909890

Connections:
+3V3: C1.1, C6.1, C7.1, C8.1, C10.1, C12.1, C14.1, C21.1, C31.1, J3.15 (VDDIO), J3.16 (VCI), L1.1, R3.2, R4.2, R6.1, R7.1, R8.1, R9.1, R11.1, R12.1, R13.1, TP4.1 (1_1), U1.5 (Vdd), U1.6 (VReg), U3.5 (OUT), U4.3 (3V3), U6.3 (VDD)
+SYS: BZ1.1 (+), C5.1, C17.1, C34.1, D5.1 (K), R5.1, U3.1 (IN), U3.3 (EN), U5.1 (SYS)
+USB_5V: C18.1, C23.1, J1.A4 (VBUS), J1.A9 (VBUS), J1.B4 (VBUS), J1.B9 (VBUS), U2.5 (VBUS), U5.10 (IN)
+VBAT: C33.1, J2.1, R18.2, U5.2 (BAT)
/AS3935_CS: R9.2, TP12.1 (1_1), U1.8 (CS), U4.19 (IO14)
/AS3935_INT: TP17.1 (1_1), U1.10 (IRQ), U4.6 (IO3)
/BTN_LEFT: C11.1, D8.1 (K), R8.2, SW2.2, U4.12 (IO0)
/BTN_MODE: C16.1, D6.1 (K), R12.2, SW4.2, U4.5 (IO2)
/BTN_RIGHT: C15.1, D7.1 (K), R11.2, SW3.2, U4.13 (IO1)
/BUZZER: R20.1, R21.1, U4.20 (IO15)
/CHG_INT: R13.2, U4.10 (IO5), U5.9 (~INT)
/EPD_BUSY: J3.9 (BUSY), U4.27 (IO21)
/EPD_CS: J3.12 (CS), TP13.1 (1_1), U4.30 (RXD0)
/EPD_D: J3.11 (D/C), TP15.1 (1_1), U4.29 (IO23)
/EPD_RES: J3.10 (RES), TP14.1 (1_1), U4.28 (IO22)
/GDR: J3.2 (GDR), Q1.1 (G), R16.1
/I2C_SCL: R3.1, TP6.1 (1_1), U4.15 (IO6), U5.8 (SCL), U6.2 (SCL)
/I2C_SDA: R4.1, TP7.1 (1_1), U4.16 (IO7), U5.7 (SDA), U6.1 (SDA)
/LED: D1.1 (K), U5.3 (~PG/GPO)
/PREV_VGH: C29.1, D2.1 (K), J3.21 (VGH)
/PREV_VGL: C26.1, D4.2 (A), J3.23 (VGL)
/PRE_USB_D+: J1.A6 (D+), J1.B6 (D+), U2.3 (I/O2)
/PRE_USB_D-: J1.A7 (D-), J1.B7 (D-), U2.1 (I/O1)
/RESE: J3.3 (RESE), Q1.2 (S), R15.1
/SPI_MISO: TP9.1 (1_1), U1.12 (MISO), U4.26 (IO20)
/SPI_MOSI: J3.14 (SDI), TP11.1 (1_1), U1.13 (MOSI/SDA), U4.24 (IO18)
/SPI_SCK: J3.13 (SCLK), TP10.1 (1_1), U1.11 (SCL), U4.25 (IO19)
/TS_BTN: R14.2, SW5.2, U5.6 (TS/MR)
/USB_D+: U2.4 (I/O2), U4.18 (IO13)
/USB_D-: U2.6 (I/O1), U4.17 (IO12)
/VBAT_ADC: C32.1, R18.1, R19.2, U4.9 (IO4)
GND: C1.2, C5.2, C6.2, C7.2, C8.2, C9.2, C10.2, C11.2, C12.2, C13.2, C14.2, C15.2, C16.2, C17.2, C18.2, C19.2, C20.2, C21.2, C22.2, C23.2, C24.2, C25.2, C26.2, C27.2, C28.1, C29.2, C31.2, C32.2, C33.2, C34.2, D3.1 (K), D6.2 (A), D7.2 (A), D8.2 (A), H1.MP, H2.MP, J1.A1 (GND), J1.A12 (GND), J1.B1 (GND), J1.B12 (GND), J1.SH (SHIELD), J2.2, J3.8 (BS), J3.17 (VSS), J3.MP, JP1.2 (B), L2.2, Q2.2 (S), R1.2, R2.2, R14.1, R15.2, R16.2, R17.1, R19.1, R21.2, SW1.1, SW2.1, SW3.1, SW4.1, SW5.1, TP3.1 (1_1), U1.2 (IN-), U1.4 (GND), U1.7 (EN), U1.9 (SI), U1.15 (AD0), U1.16 (AD1), U1.17 (GNDPAD), U2.2 (GND), U3.2 (GND), U4.1 (GND), U4.2 (GND), U4.11 (GND), U4.14 (GND), U4.36 (GND), U4.37 (GND), U4.38 (GND), U4.39 (GND), U4.40 (GND), U4.41 (GND), U4.42 (GND), U4.43 (GND), U4.44 (GND), U4.45 (GND), U4.46 (GND), U4.47 (GND), U4.48 (GND), U4.49 (GND), U4.50 (GND), U4.51 (GND), U4.52 (GND), U4.53 (GND), U5.5 (GND), U5.11 (GND), U6.4 (VSS)
unnamed: BZ1.2 (-), D5.2 (A), Q2.3 (D)
unnamed: D1.2 (A), R5.2
unnamed: C30.2, D2.2 (A), L1.2, Q1.3 (D)
unnamed: C30.1, D3.2 (A), D4.1 (K)
unnamed: J1.A5 (CC1), R1.1
unnamed: J1.B5 (CC2), R2.1
unnamed: C27.1, J3.24 (VCOM)
unnamed: C22.1, J3.18 (VDD)
unnamed: C24.1, J3.20 (VSH1)
unnamed: C28.2, J3.5 (VSH2)
unnamed: C25.1, J3.22 (VSL)
unnamed: JP1.1 (A), U4.23 (IO9)
unnamed: Q2.1 (G), R20.2
unnamed: C13.1, U1.1 (ACG)
unnamed: C19.1, C20.1, L2.1, R17.2, U1.3 (IN+)
unnamed: C9.1, R7.2, SW1.2, U4.8 (EN)
unnamed: R6.2, U4.22 (IO8)

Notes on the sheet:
SPI 1-2Mhz NO 500Mhz
E-Paper: GDEY0154D67
(PD on boot = USB)
USB-C & BAT -> 3V3
ESP32 C6
Lightning Sensor
EPD
BTNs
SELECT SPI
Temp/Hum
VREG=OFF
Buzzer

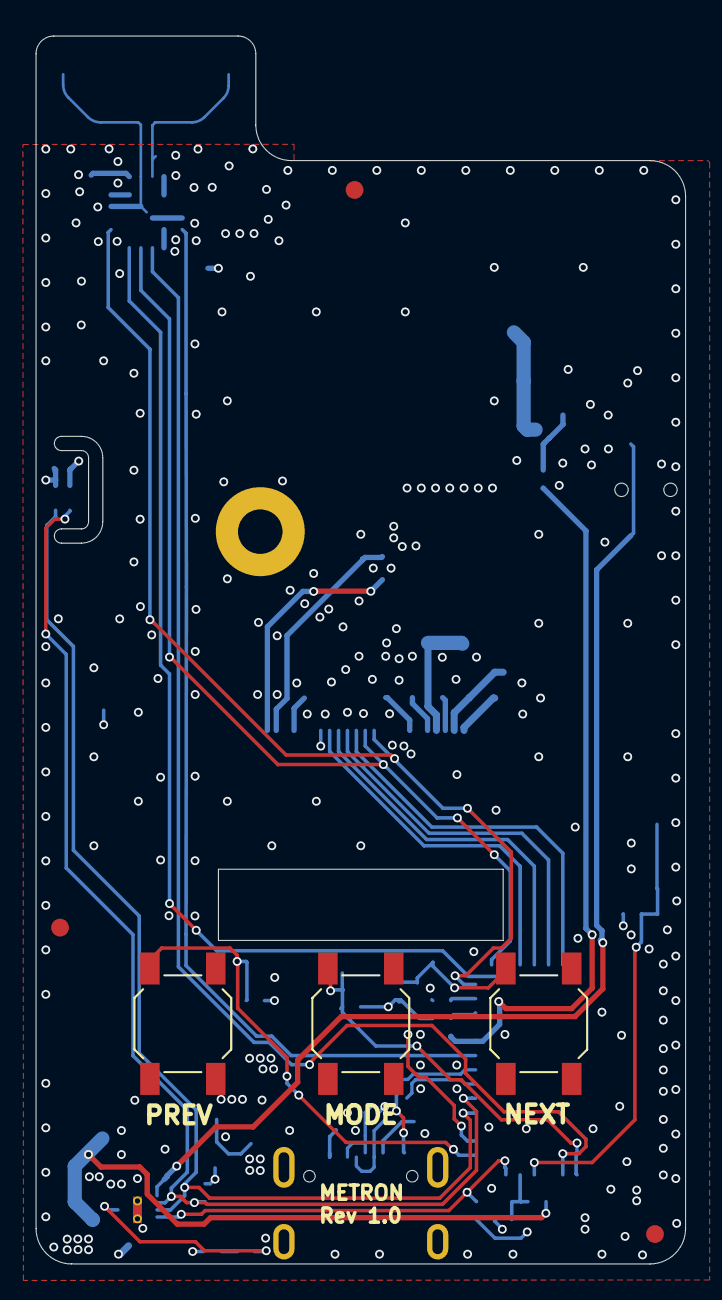
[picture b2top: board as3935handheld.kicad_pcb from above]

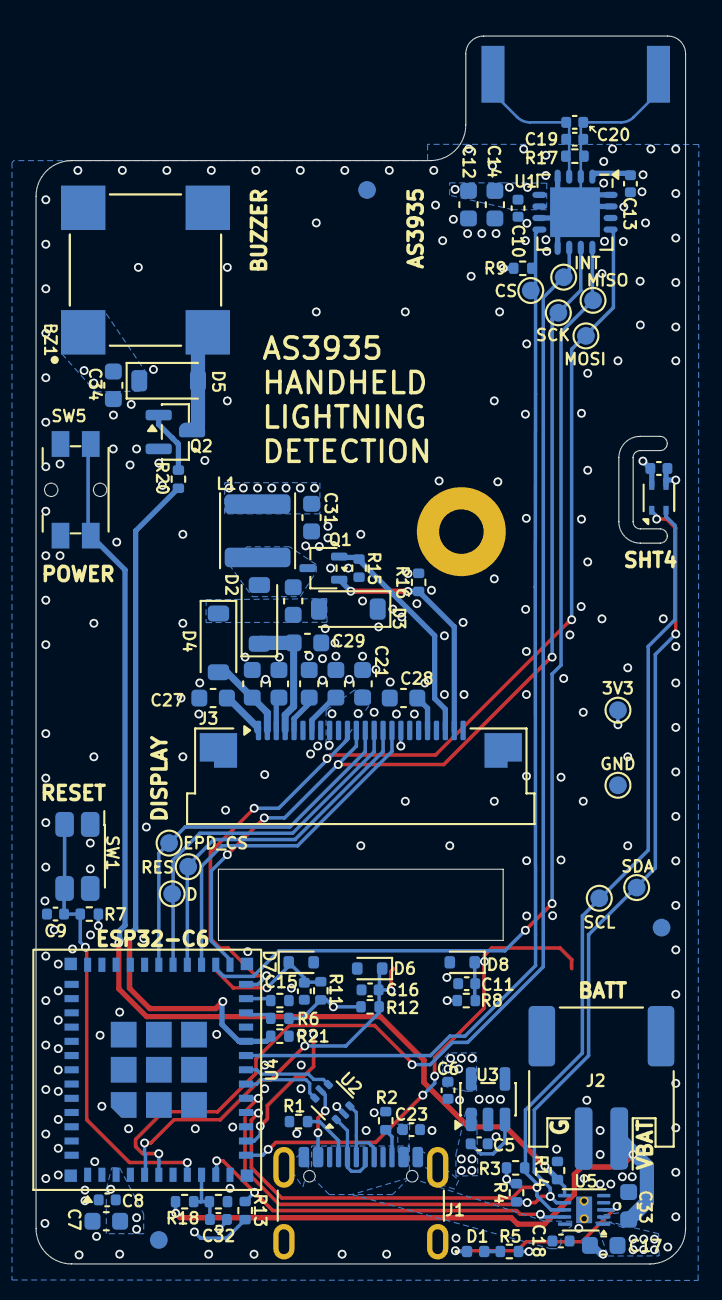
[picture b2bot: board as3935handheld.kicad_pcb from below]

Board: 4 copper layers, 36.5 x 69.0 mm, 93 parts (88 on the bottom side), 49 nets.

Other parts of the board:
DISP_REF: Display_GDEY0154D67_Mech

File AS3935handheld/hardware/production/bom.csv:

Designator,Footprint,Quantity,Value,LCSC Part #
BZ1,CUI_CMT-8530S-SMT,1,CMT-8530S,CMT-8530S-SMT-TR
"C1, C10, C11, C15, C16, C23, C32, C8",0402,8,100nF,
C12,0603,1,4.7uF,
C13,0402,1,10uF,
"C14, C21, C22, C24, C25, C26, C27, C28, C29",0603,9,1uF 25V,CGA3E1X7R1E105K080AC
"C17, C33, C34",0603,3,10uF,
"C18, C5, C6, C9",0402,4,1uF,
C19,0402,1,680pF C0G,GCM1555C1H681FA16D
C20,0402,1,270pF C0G,GRT1555C1H271FA02D
"C30, C31",0603,2,4.7uF 25V,C1608X5R1E475K080AC
C7,0603,1,22uF,
D1,0402,1,Red Led,QBLP595-R-2897
"D2, D3, D4, D5",D_SOD-123,4,MBR0530,C82046
"D6, D7, D8",D_SOD-523,3,ESD5Z3.3T1G,ESD5Z3.3T1G
J1,USB_C_Receptacle_GCT_USB4105-xx-A_16P_TopMnt_Horizontal,1,USB_C_Receptacle_USB2.0_16P,USB4105-GF-A
J2,JST_PH_S2B-PH-SM4-TB_1x02-1MP_P2.00mm_Horizontal,1,Batt,S2B-PH-SM4-TB
J3,Amphenol_F32Q-1A7x1-11024_1x24-1MP_P0.5mm_Horizontal_RevPinout,1,FPC_24_Epaper_SSD1680,F32Q-1A7H1-11024
L1,L_APV_ANR4030,1,47uH 0.5A,C223059
L2,Coilcraft_MA5532-AE_RFID,1,MA5532-AE,MA5532-AED
Q1,SOT-323_SC-70,1,Si1308EDL,SI1308EDL-T1-BE3
Q2,SOT-23,1,AO3400A,AO3400A
"R1, R2",0402,2,5k1,
"R11, R12, R13, R14, R21, R6, R7, R8, R9",0402,9,10k,
R15,0402,1,2.2R,
"R16, R18, R19",0402,3,1M,
R17,0402,1,10k 1%,
R20,0402,1,100,
"R3, R4",0402,2,4k7,
R5,0402,1,680,
SW1,SW_SPST_EVQP7A,1,RST_BTN,EVQ-P7A01P
SW2,SW_SPST_SKQG_WithStem,1,BTN_LEFT,SKQGABE010
SW3,SW_SPST_SKQG_WithStem,1,BTN_RIGHT,SKQGABE010
SW4,SW_SPST_SKQG_WithStem,1,BTN_MODE,SKQGABE010
SW5,Panasonic_EVQPUM_EVQPUD,1,PWR_BTN,C388885
U1,MLPQ-16-1EP_4x4mm_P0.65mm_EP2.8x2.8mm,1,AS3935,AS3935-BQFT
U2,SOT-666,1,USBLC6-2P6,C15999
U3,SOT-23-5,1,TLV75533PDBV,C404027
U4,ESP32-C6-MINI-1U,1,ESP32-C6-MINI-1,ESP32-C6-MINI-1U-H4
U5,Texas_DLH0010A_WSON-10-1EP_2.2x2mm_P0.4mm_EP0.9x1.5mm_ThermalVias,1,BQ25186DLHR,BQ25186DLHR
U6,Sensirion_DFN-4_1.5x1.5mm_P0.8mm_SHT4x_NoCentralPad,1,SHT40-AD1B-R2,C2909890
